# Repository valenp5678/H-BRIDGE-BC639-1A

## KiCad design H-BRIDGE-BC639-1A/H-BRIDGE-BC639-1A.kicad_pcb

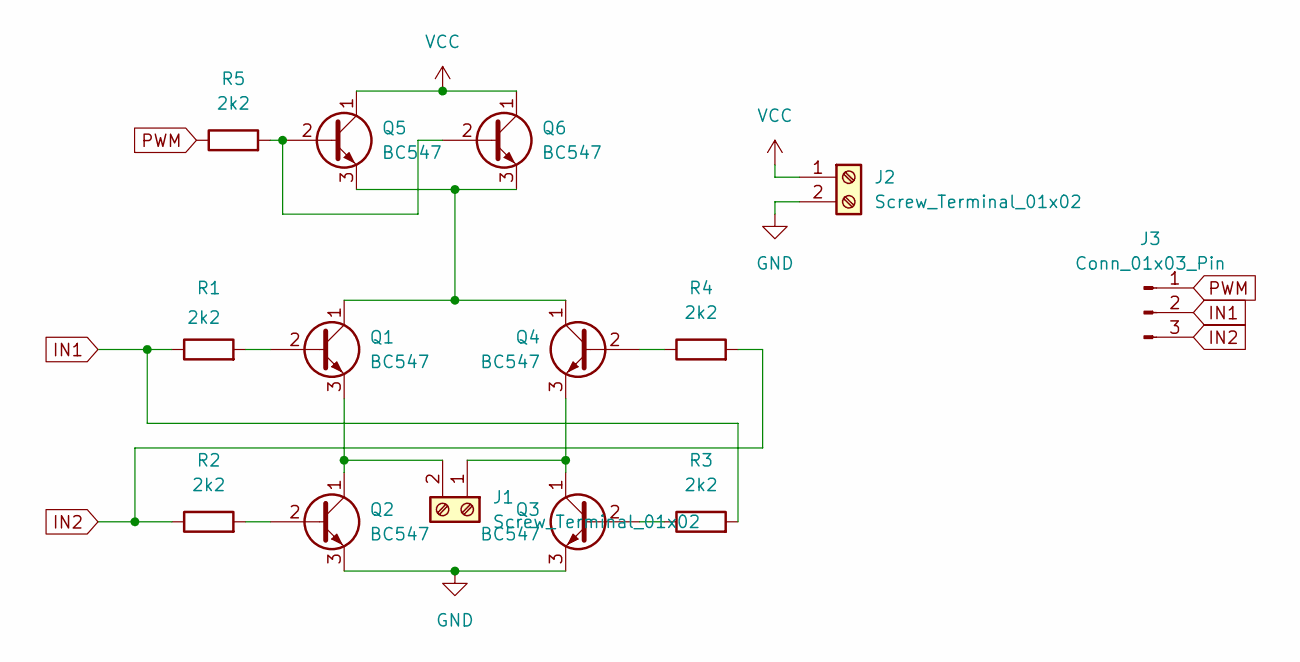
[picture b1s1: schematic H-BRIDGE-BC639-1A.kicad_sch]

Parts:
J1, J2: Screw_Terminal_01x02; TerminalBlock_bornier-2_P5.08mm
J3: Conn_01x03_Pin; PinHeader_1x03_P2.54mm_Vertical
Q1, Q2, Q3, Q4, Q5, Q6: BC547; TO-92_Inline_Wide
R1, R2, R3, R4, R5: 2k2; R_Axial_DIN0204_L3.6mm_D1.6mm_P7.62mm_Horizontal

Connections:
GND: J2.2, Q2.3 (E), Q3.3 (E)
IN1: J3.2, R1.1, R3.2
IN2: J3.3, R2.1, R4.2
unnamed: J1.1, Q3.1 (C), Q4.3 (E)
unnamed: J1.2, Q1.3 (E), Q2.1 (C)
unnamed: Q1.2 (B), R1.2
unnamed: Q1.1 (C), Q4.1 (C), Q5.3 (E), Q6.3 (E)
unnamed: Q2.2 (B), R2.2
unnamed: Q3.2 (B), R3.1
unnamed: Q4.2 (B), R4.1
unnamed: Q5.2 (B), Q6.2 (B), R5.2
PWM: J3.1, R5.1
VCC: J2.1, Q5.1 (C), Q6.1 (C)

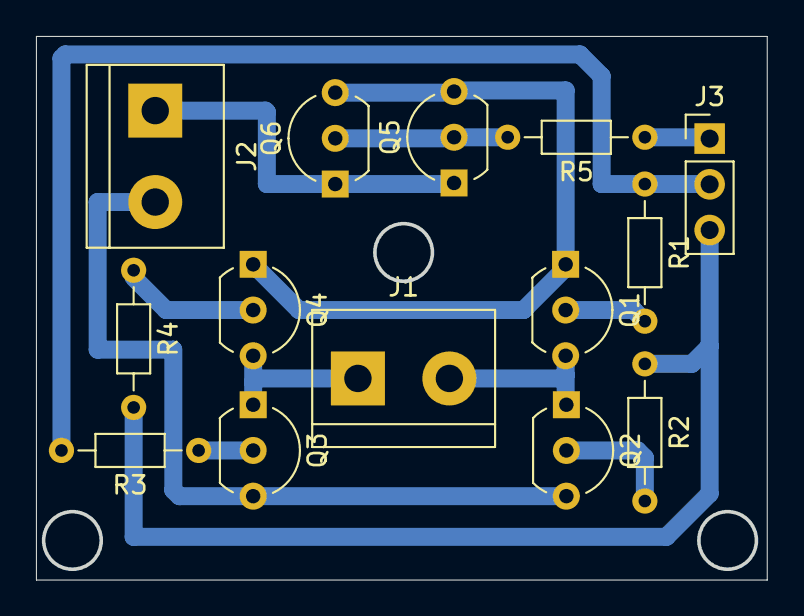
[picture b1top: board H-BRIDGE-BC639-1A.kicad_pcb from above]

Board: 2 copper layers, 40.5 x 30.1 mm, 14 parts (0 on the bottom side), 13 nets.

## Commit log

2024-03-26 puente h bc549 terminada
